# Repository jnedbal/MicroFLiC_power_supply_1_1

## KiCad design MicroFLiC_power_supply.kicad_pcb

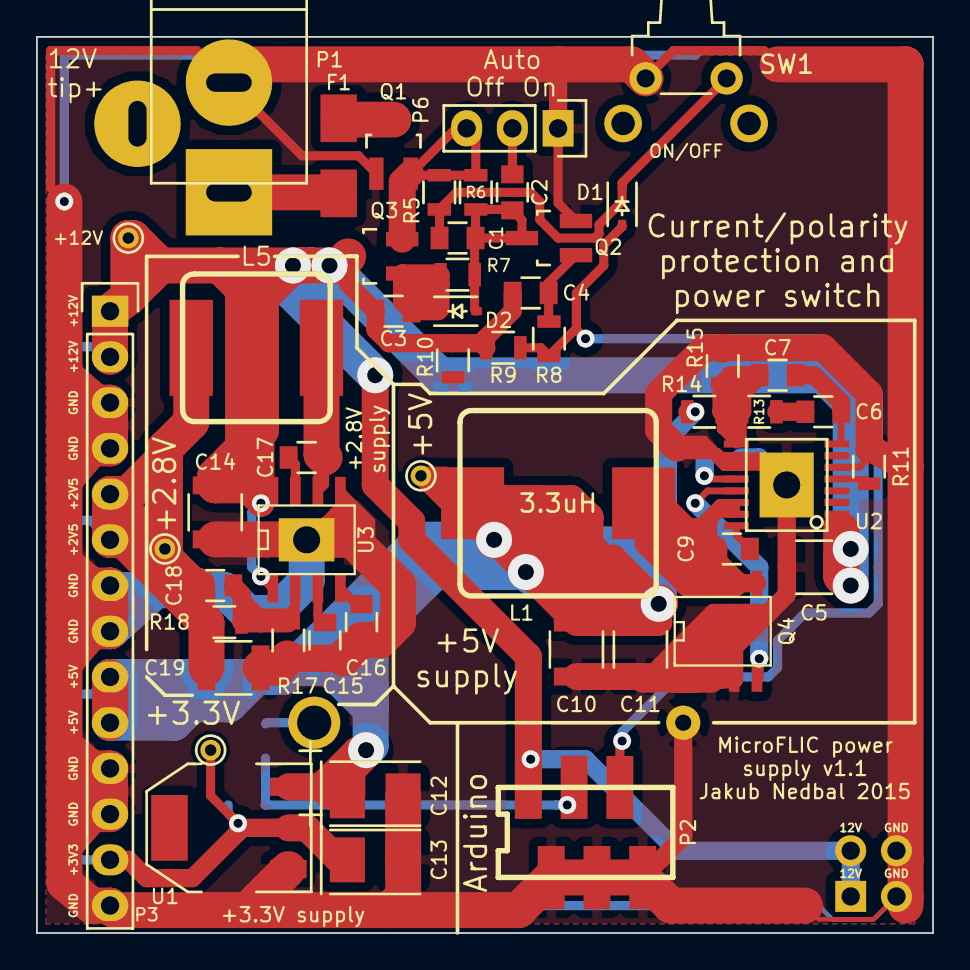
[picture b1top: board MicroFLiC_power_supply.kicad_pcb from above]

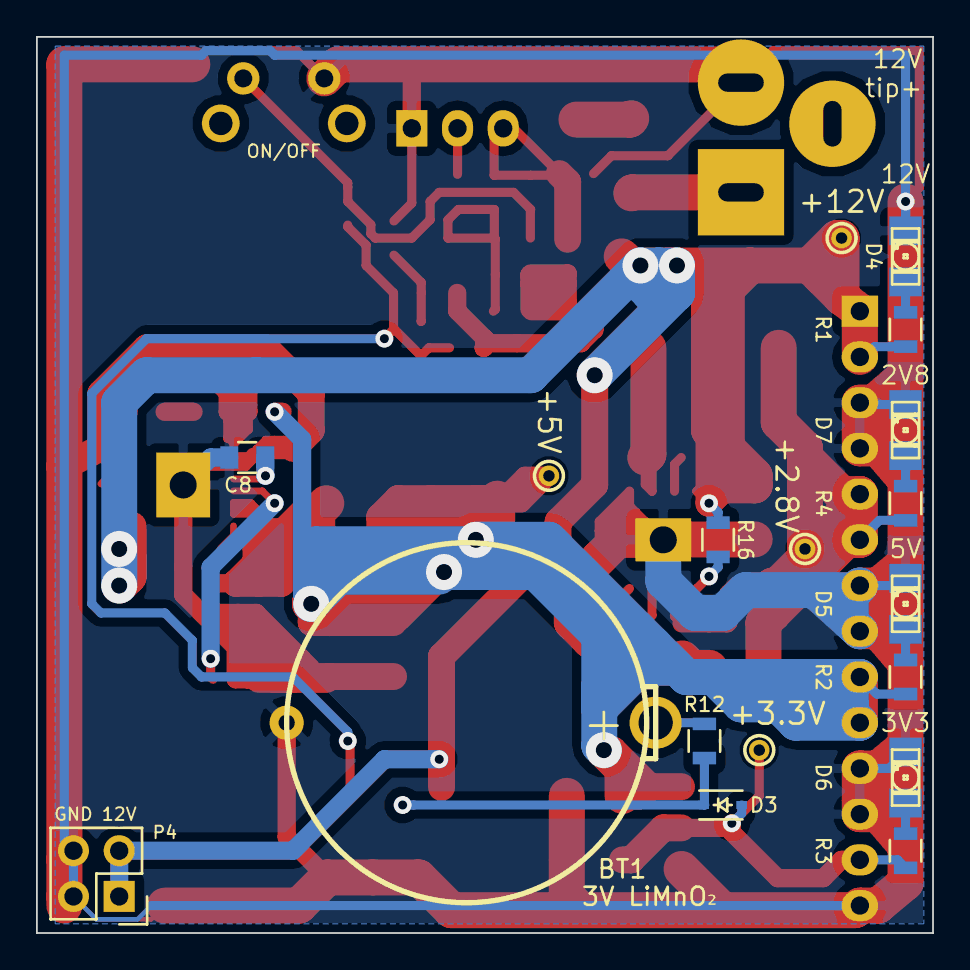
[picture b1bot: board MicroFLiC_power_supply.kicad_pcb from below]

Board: 2 copper layers, 49.8 x 49.8 mm, 65 parts (14 on the bottom side), 34 nets.

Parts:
BT1: 3V LiMnO₂; ML2016
C1, C8, C15: 1u/50V; C_0805
C2, C9, C17: 100n; C_0805
C3: 10n; C_0805
C4: 4u7/25V; C_0805
C5, C14: 22u/25V; C_1210
C6: 680p; C_0805
C7: 1p5; C_0805
C10, C11, C19: 47u/16V; C_1210
C12, C13: 10u/10V/0.15Ω<ESR<0.5Ω; TantalC_SizeB_EIA-3528_Reflow
C16: 8n2; C_0805
C18: 4p7; C_0805
D1, D2, D3: 1N4148; SOD-323
D4, D5, D6, D7: LED; LED-1206
F1: F5A; Fuse_SMD1206_HandSoldering
L1: 3.3uH; IHLP-4040DZ-01
L5: 2.2uH; IHLP-3232CZ-11
P1: DC jack; JACK_ALIM
P2: 6-way Micro-MaTch; 7-188275-6
P3: 1x14 socket strip; ESQ-114-33-S-G
P4: 2x2 socket strip; ESQ-102-33-D-G
P6: 1x3 header strip; Pin_Header_Straight_1x03
PP1: +12V; PINTST
PP2: +5V; PINTST
PP3: +3.3V; PINTST
PP4: +2.8V; PINTST
Q1, Q3: SI2369; SOT23GDS
Q2: TSM2314; SOT23GDS
Q4: IRF8721; SO8_FDS6298
R1, R10, R16: 10k; R_0805
R2, R15: 3k; R_0805
R3: 1k5; R_0805
R4: 1k; R_0805
R5, R6, R7, R9: 100k; R_0805
R8: 270k; R_0805
R11, R13: 82k; R_0805
R12: 470R; R_0805
R14: 22k; R_0805
R17: 12k; R_0805
R18: 33k; R_0805
SW1: Tactile switch R/A; tactileSwitchRA
U1: AP1117E33; SOT-223
U2: ADP2381; SSOP-16(EP)
U3: TPS54428; PDSO8

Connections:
+2V5: C18.1, C19.1, L5.2, P3.5, P3.6, PP4.1, R4.1, R18.1
+3V3: C13.1, D3.2, P3.13, PP3.1, R3.1, U1.2
+5VP: C10.1, C11.1, C12.1, L1.2, P3.9, P3.10, PP2.1, R2.1, R14.1, U1.3
+12V: C3.1, C4.1, C5.1, C14.1, P2.1, P3.1, P3.2, P4.1, P4.2, PP1.1, Q3.D, R1.1, R9.1, R10.1, R16.1, U2.1, U2.2, U3.8
+BATT: D3.1, P2.3, R12.1
/Power Supply/BST: C9.1, U2.16
/Power Supply/C7R8: C6.2, R13.1
/Power Supply/COMP: C6.1, C7.1, U2.8
/Power Supply/EN: R16.2, U3.1
/Power Supply/FB: C7.2, R13.2, R14.2, R15.1, U2.9
/Power Supply/LD: Q4.G, U2.13
/Power Supply/RT: R11.2, U2.5
/Power Supply/SS: C16.1, U3.4
/Power Supply/SW2.8: C17.1, L5.1, U3.6
/Power Supply/SW5: C9.2, L1.1, Q4.D, U2.14, U2.15
/Power Supply/VBST: C17.2, U3.7
/Power Supply/VFB: C18.2, R17.1, R18.2, U3.2
/Power Supply/VREG2.8: C15.1, U3.3
/Power Supply/VREG5: C8.1, U2.12
/electronicSwitch/AUTO: C2.2, P6.2
/electronicSwitch/CURLIM: C3.2, D2.1, Q3.G, R7.2
/electronicSwitch/DELAYED_OFF: C4.2, Q2.G, R8.1
/electronicSwitch/MCU_OFF: D1.2, P2.5, R8.2, R9.2
/electronicSwitch/PUSHBUTTON: C1.2, D1.1, R5.2, SW1.2
/electronicSwitch/V_5AMP: F1.2, Q1.D
/electronicSwitch/V_IN: F1.1, P1.1
/electronicSwitch/V_PROTECTED: P6.3, Q1.S, Q3.S, R5.1, R6.1
GND: BT1.2, C5.2, C8.2, C10.2, C11.2, C12.2, C13.2, C14.2, C15.2, C16.2, C19.2, D4.1, D5.1, D6.1, D7.1, P1.2, P2.2, P2.4, P2.6, P3.3, P3.4, P3.7, P3.8, P3.11, P3.12, P3.14, P4.3, P4.4, P6.1, Q1.G, Q2.S, Q4.S, R10.2, R11.1, R15.2, R17.2, SW1.1, U1.1, U2.6, U2.10, U2.11, U2.17, U3.5, U3.9
unnamed: BT1.1, R12.2
unnamed: C1.1, C2.1, D2.2, Q2.D, R6.2, R7.1
unnamed: D4.2, R1.2
unnamed: D5.2, R2.2
unnamed: D6.2, R3.2
unnamed: D7.2, R4.2

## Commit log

2016-01-08 Fixed component references, diode orientation, part numbers
2016-01-08 Got rid of useless files
2016-01-19 Added load resistor. Changed part references in consequence.
2016-02-19 Fixed 12k resistor, added .gitignore
2016-02-22 Changed BAR43S diode into 1N4148 for minimum leakage current.
2016-03-02 Added detailed part descriptions
2016-03-02 Renamed all files to remove version number
2016-03-10 Removed _1_1 suffix from filenames
2016-03-18 Changed SOD-323 package for easier soldering, fixed Avago->Broadcom LED manufacturer
